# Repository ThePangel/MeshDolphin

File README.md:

# MeshDolphin
A meshtastic Flipper zero GPIO module and app

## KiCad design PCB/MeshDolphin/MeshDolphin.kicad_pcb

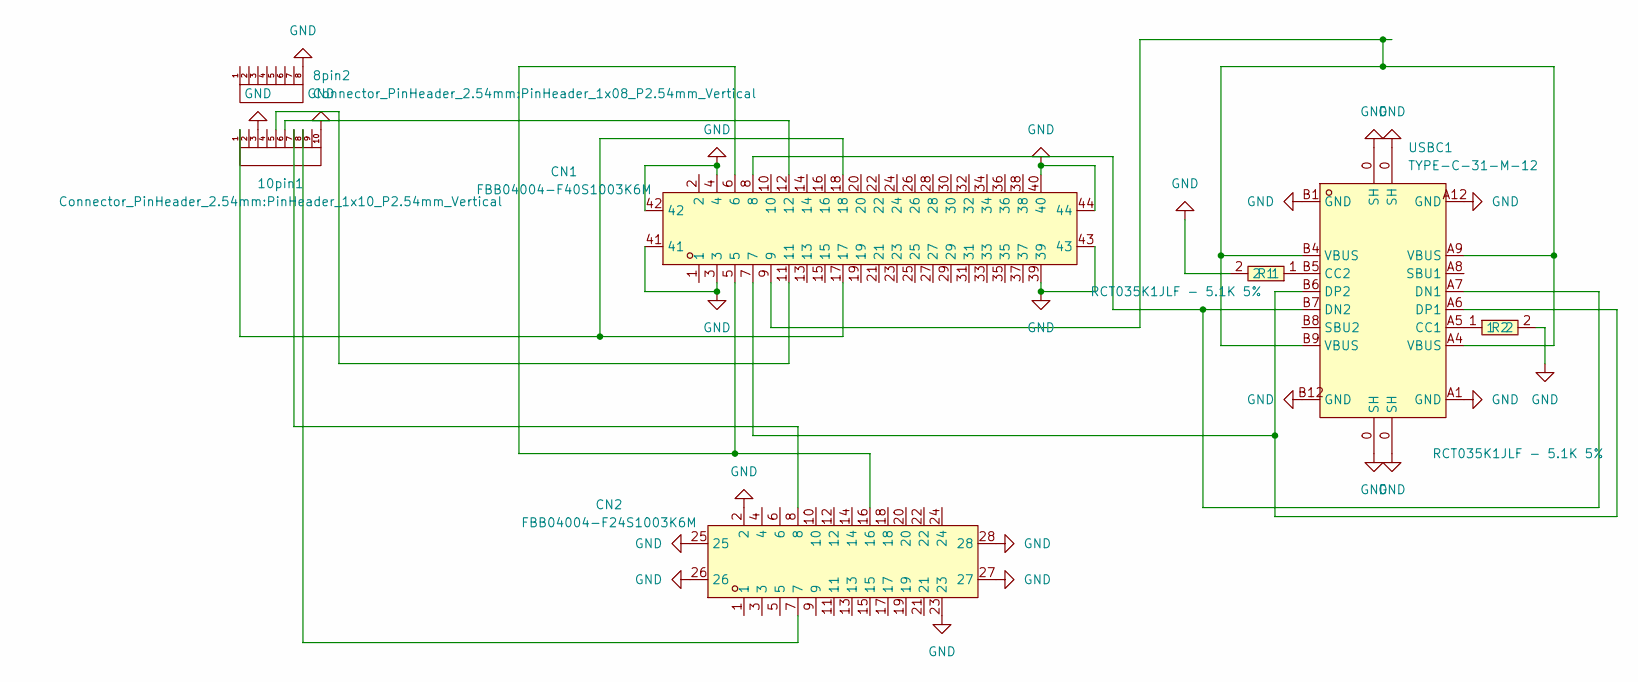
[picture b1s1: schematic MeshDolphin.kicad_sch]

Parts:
8pin2: PinHeader_1x08_P2.54mm_Vertical
10pin1: PinHeader_1x10_P2.54mm_Vertical
CN1: FBB04004-F40S1003K6M; CONN-SMD_FBB04004-F40S1003K6M; LCSC Part C691131
CN2: FBB04004-F24S1003K6M; CONN-SMD_FBB04004-F24S1003K6M; LCSC Part C691129
R1, R2: RCT035K1JLF - 5.1K 5%; R0603; LCSC Part C177348
USBC1: TYPE-C-31-M-12; USB-C_SMD-TYPE-C-31-M-12; LCSC Part C165948

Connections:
GND: 8pin2.8, 10pin1.3, 10pin1.10, CN1.3, CN1.4, CN1.39, CN1.40, CN1.41, CN1.42, CN1.43, CN1.44, CN2.2, CN2.23, CN2.25, CN2.26, CN2.27, CN2.28, R1.2, R2.2, USBC1.0 (SH), USBC1.A1 (GND), USBC1.A12 (GND), USBC1.B1 (GND), USBC1.B12 (GND)
unnamed: 10pin1.1, CN1.17, CN1.18
unnamed: 10pin1.5, CN1.11
unnamed: 10pin1.6, CN1.12
unnamed: 10pin1.7, CN2.8
unnamed: 10pin1.8, CN2.7
unnamed: CN1.5, CN1.6, CN2.16
unnamed: CN1.9, USBC1.A4 (VBUS), USBC1.A9 (VBUS), USBC1.B4 (VBUS), USBC1.B9 (VBUS)
unnamed: R2.1, USBC1.A5 (CC1)
unnamed: R1.1, USBC1.B5 (CC2)
unnamed: CN1.8, USBC1.A7 (DN1), USBC1.B7 (DN2)
unnamed: CN1.7, USBC1.A6 (DP1), USBC1.B6 (DP2)

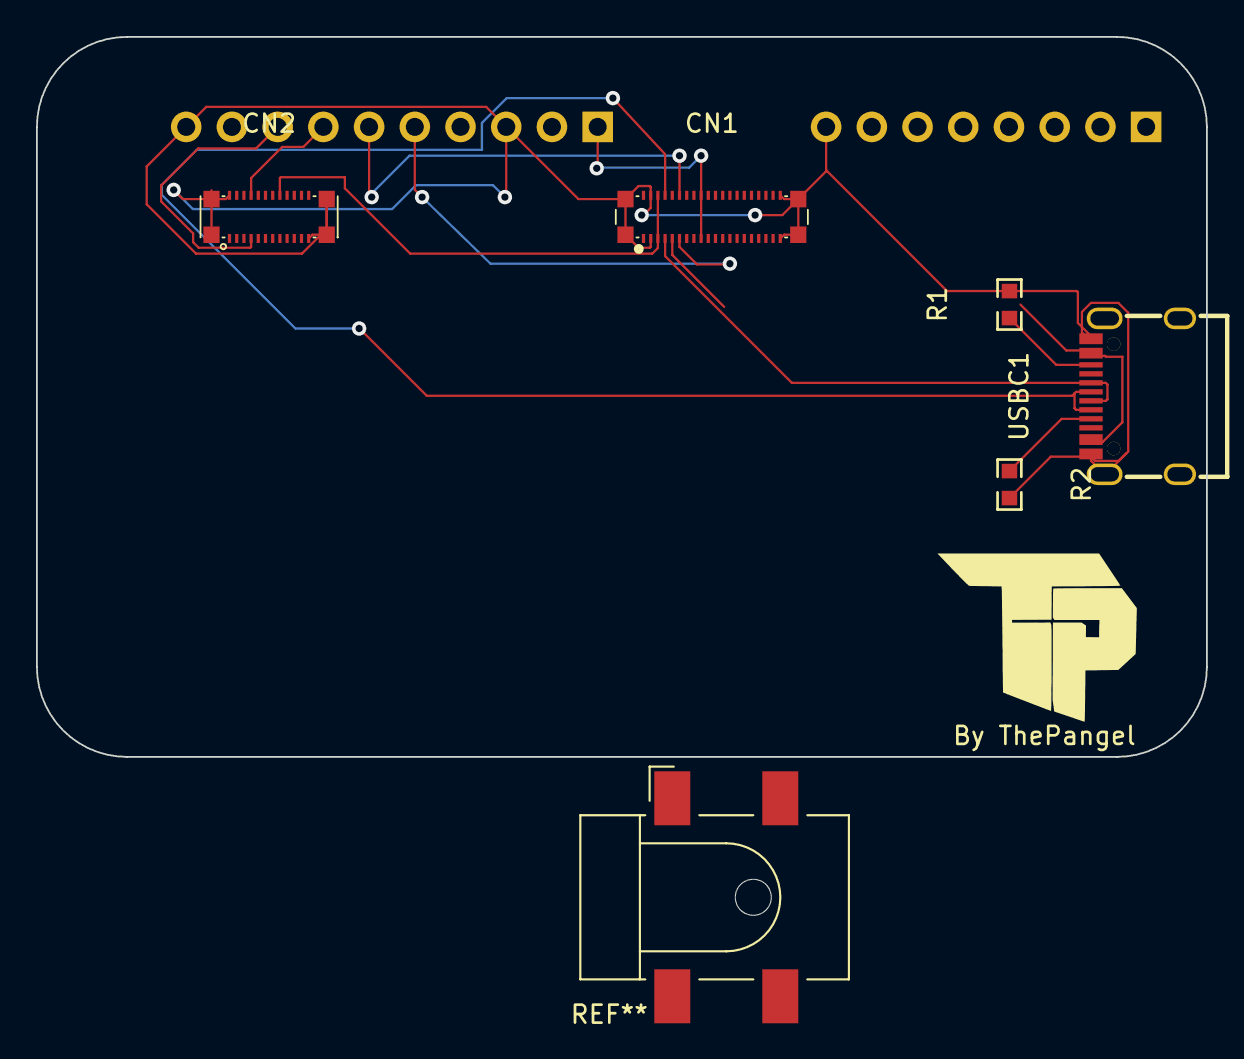
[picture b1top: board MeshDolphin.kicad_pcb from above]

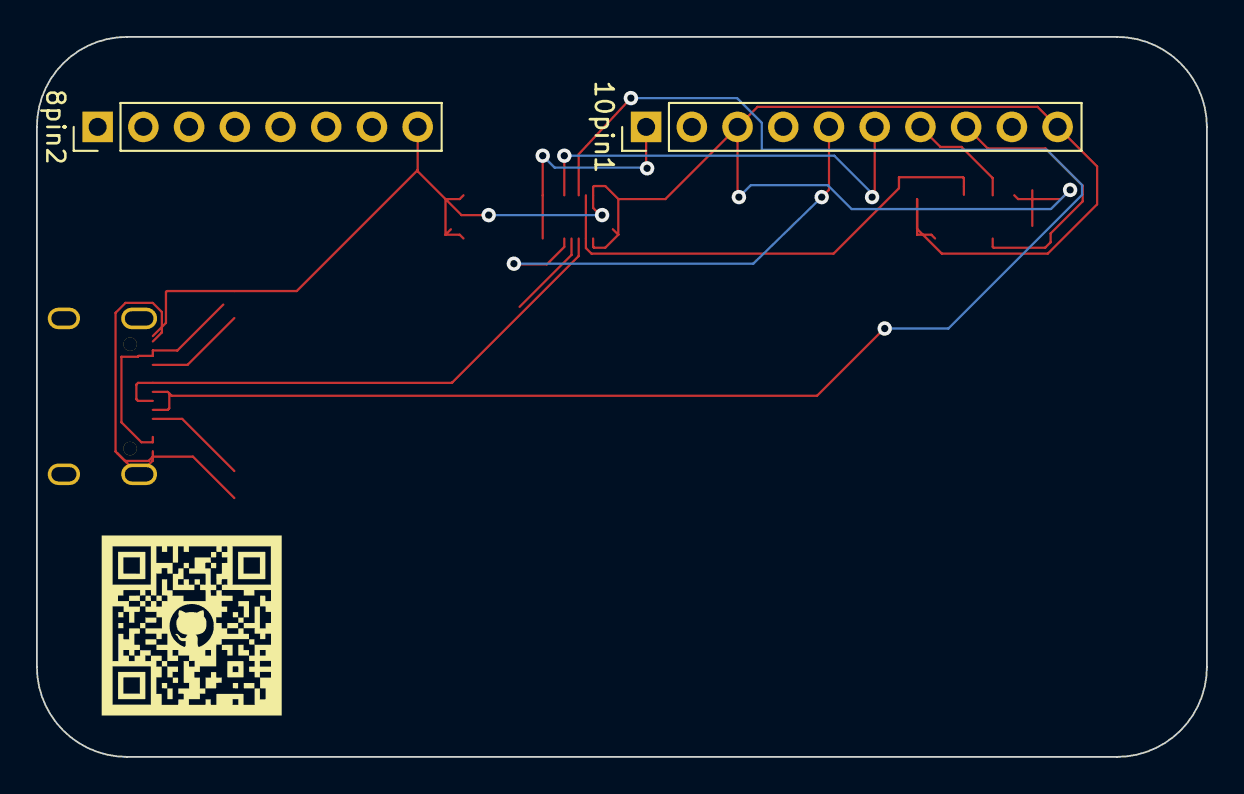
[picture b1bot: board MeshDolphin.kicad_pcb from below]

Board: 2 copper layers, 65.0 x 40.0 mm, 8 parts (2 on the bottom side), 12 nets.

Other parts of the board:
REF: LOGO

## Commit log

2025-08-14 Created KiCad Project
2025-08-14 Initial pcb design
